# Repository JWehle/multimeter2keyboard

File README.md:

# multimeter2keyboard
A board that reads 38XR-A multimeter infrared port outputs and converts them to PC keyboard inputs.

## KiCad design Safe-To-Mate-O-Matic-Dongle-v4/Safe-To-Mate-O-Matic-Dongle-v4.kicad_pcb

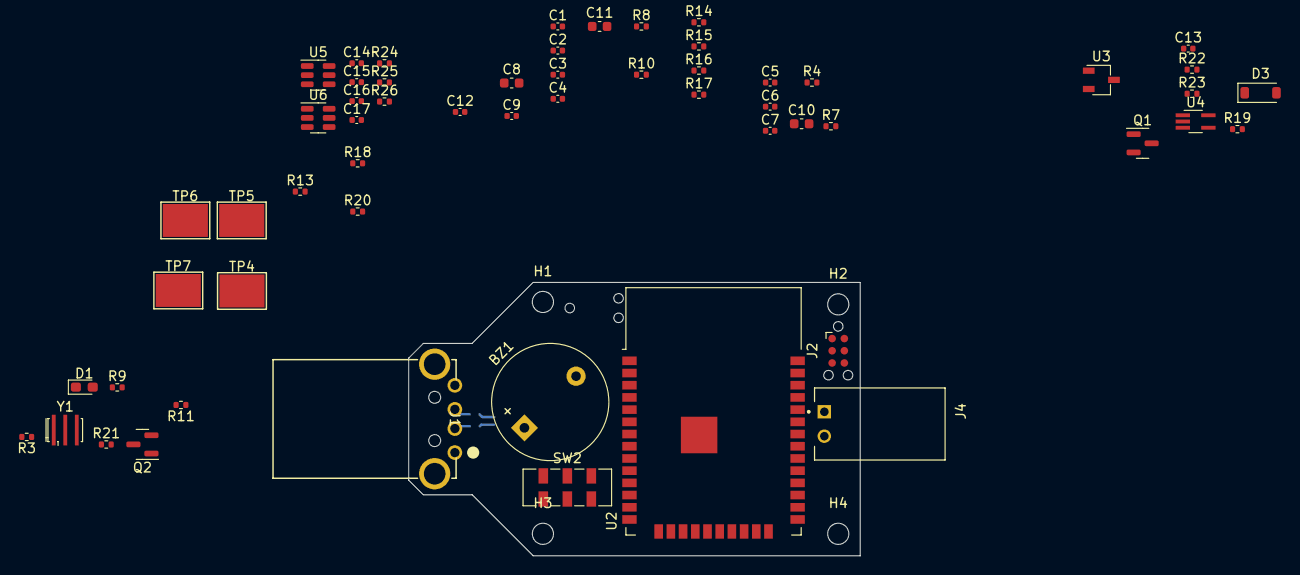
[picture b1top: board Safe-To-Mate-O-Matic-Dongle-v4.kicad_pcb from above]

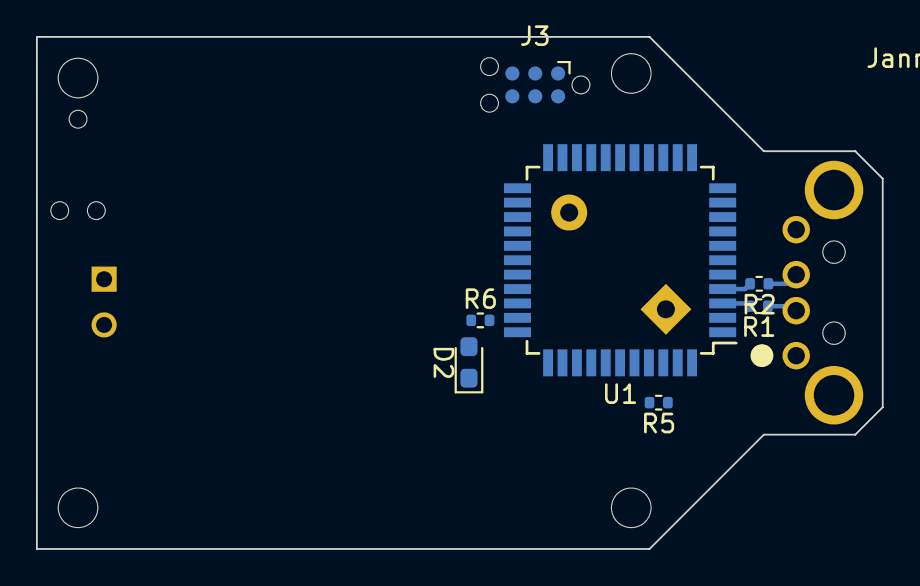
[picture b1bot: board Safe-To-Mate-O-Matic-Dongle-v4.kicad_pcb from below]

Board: 4 copper layers, 47.0 x 28.4 mm, 68 parts (7 on the bottom side), 46 nets.

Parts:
BZ1: WST-1210T; Buzzer_12x9.5RM7.6
C1, C2, C3, C4: 1uF; C_0402_1005Metric
C5, C6, C7, C9, C12, C13, C14, C15, C16, C17: 0.1uF; C_0402_1005Metric
C8, C10, C11: 10uF; C_0603_1608Metric
D1, D2: GREEN LED; LED_0603_1608Metric_Pad1.05x0.95mm_HandSolder
D3: 1N4148W; D_SOD-123
H1, H2, H3, H4: M2; MountingHole_2.2mm_M2
J1: USB_A; USB_MALE_A_480370001
J2, J3: TC2030-IDC-NL; Tag-Connect_TC2030-IDC-NL_2x03_P1.27mm_Vertical
J4: 103906-1; TE_103906-1
Q1, Q2: MMBT3904; SOT-23
R1, R2, R5: 22; R_0402_1005Metric
R3, R4, R7, R8, R14, R15, R16, R17, R18, R19, R20, R21, R22, R23, R24, R26: 10K; R_0402_1005Metric
R6, R9: 1K; R_0402_1005Metric
R10, R11, R25: 0; R_0402_1005Metric
R13: 1Meg; R_0402_1005Metric
SW2: JS202011JCQN; SW_DPDT_CK_JS202011JCQN
TP4, TP5, TP6, TP7: 5016; TestPoint_Keystone_5016_Compact
U1: ATmega32U4-A; TQFP-44_10x10mm_P0.8mm
U2: ESP32-WROOM-32D; ESP32-WROOM-32D_no_vias
U3: AP2138N-3.3TRG1; TSOT-23
U4: 74AHC1G14SE-7; SOT-353_SC-70-5_Handsoldering
U5, U6: SN74LVC1T45DBV; SOT-23-6
Y1: CSTNE16M0V530000R0; Resonator_SMD_Murata_CSTxExxV-3Pin_3.0x1.1mm_HandSoldering

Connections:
+3.3V: C8.1, C9.1, C12.1, C15.1, C17.1, J2.2, R7.1, R8.1, R10.1, R15.1, R20.1, R23.1, TP7.1, U2.2 (VDD), U4.5 (VCC), U5.6 (VCCB), U6.6 (VCCB)
+5V: C2.1, C4.1, C5.1, C6.1, C7.1, C10.1, C14.1, C16.1, J1.1 (VBUS), J3.2, R3.1, R4.1, R14.1, R21.1, R25.2, TP6.1, U1.2 (UVCC), U1.7 (VBUS), U1.14 (VCC), U1.24 (AVCC), U1.34 (VCC), U1.44 (AVCC), U3.3 (VI), U5.1 (VCCA), U6.1 (VCCA)
/+3.3V_PRE: C11.1, R10.2, U3.2 (VO)
/ATMEGA_LED: R6.2, U1.32 (PC7)
/ESP32_LED: R9.2, U2.24 (IO2)
ATMEGA_BUTTON: Q2.3 (C), R21.2, U1.18 (PD0)
ATMEGA_LN: SW2.2 (B), U1.19 (PD1)
ESP32_BOOT0: J2.5, R8.2, U2.25 (IO0)
ESP32_BUTTON: Q1.3 (C), R20.2, U2.13 (IO14)
ESP32_EN: J2.4, R7.2, U2.3 (EN)
ESP32_LN: SW2.5 (B), U2.16 (IO13)
GND: BZ1.2 (+), C1.2, C2.2, C3.2, C4.2, C5.2, C6.2, C7.2, C8.2, C9.2, C10.2, C11.2, C12.2, C13.2, C14.2, C15.2, C16.2, C17.2, D1.1 (K), D2.1 (K), J1.4 (GND), J2.6, J3.6, J4.2, Q1.2 (E), Q2.2 (E), R11.2, R13.2, R16.2, R17.2, R24.2, R26.2, TP4.1, TP5.1, U1.5 (UGND), U1.15 (GND), U1.23 (GND), U1.35 (GND), U1.43 (GND), U2.1 (GND), U2.15 (GND), U2.38 (GND), U2.39 (GND), U3.1 (GND), U4.3 (GND), U5.2 (GND), U6.2 (GND), Y1.2
MISO: J3.1, U1.11 (PB3)
MOSI: J3.4, U1.10 (PB2)
unnamed: BZ1.1 (-), R5.1
unnamed: D1.2 (A), R9.1
unnamed: D2.2 (A), R6.1
unnamed: D3.2 (A), J4.1, R22.2, R23.2
unnamed: C13.1, D3.1 (K), R22.1, U4.2
unnamed: J1.3 (D+), R2.1
unnamed: J1.2 (D-), R1.1
unnamed: Q1.1 (B), R19.1
unnamed: Q2.1 (B), R18.1
unnamed: R18.2, R19.2, U4.4
unnamed: R14.2, SW2.1 (A)
unnamed: R16.1, SW2.3 (C)
unnamed: R15.2, SW2.4 (A)
unnamed: R17.1, SW2.6 (C)
unnamed: C1.1, U1.42 (AREF)
unnamed: R2.2, U1.4 (D+)
unnamed: R1.2, U1.3 (D-)
unnamed: R5.2, U1.29 (PB5)
unnamed: C3.1, U1.6 (UCAP)
unnamed: U1.17 (XTAL1), Y1.3
unnamed: U1.16 (XTAL2), Y1.1
unnamed: R4.2, U1.33 (~HWB/PE2)
unnamed: R25.1, U5.5 (DIR)
unnamed: R11.1, U6.5 (DIR)
RESET: J3.5, R3.2, U1.13 (~RESET)
RX: U1.20 (PD2), U6.3 (A)
RXD0: J2.3, U2.34 (RXD0/IO3)
RXD2: U2.27 (IO16), U5.4 (B)
SCK: J3.3, U1.9 (PB1)
TX: R24.1, U1.21 (PD3), U5.3 (A)
TXD0: J2.1, U2.35 (TXD0/IO1)
TXD2: R26.1, U2.28 (IO17), U6.4 (B)

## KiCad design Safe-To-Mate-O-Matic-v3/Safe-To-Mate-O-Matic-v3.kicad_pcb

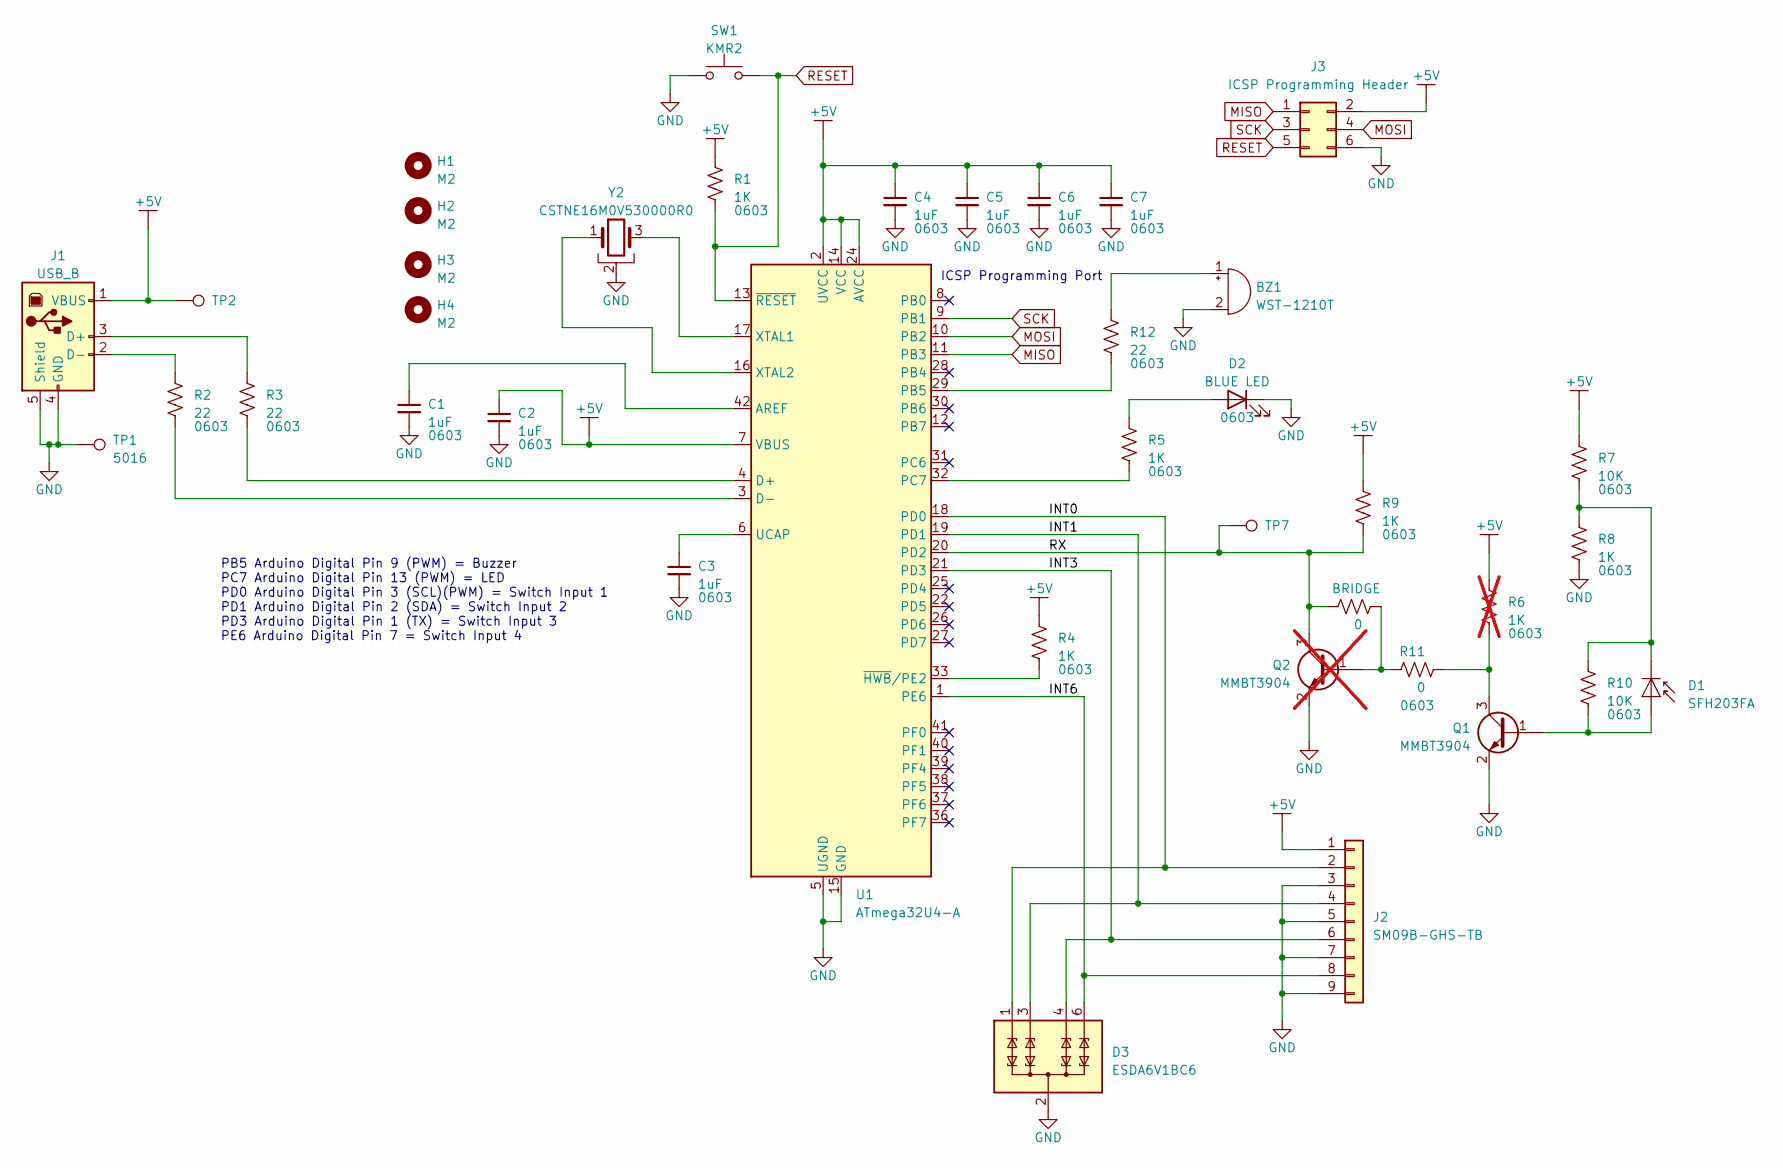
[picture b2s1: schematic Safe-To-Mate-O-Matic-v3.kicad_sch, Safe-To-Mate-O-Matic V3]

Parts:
BRIDGE: 0; R_0603_1608Metric_Pad0.98x0.95mm_HandSolder
BZ1: WST-1210T; Buzzer_12x9.5RM7.6
C1, C2, C3, C4, C5, C6, C7: 1uF; C_0603_1608Metric_Pad1.08x0.95mm_HandSolder
D1: SFH203FA; LED_D5.0mm_IRGrey
D2: BLUE LED; LED_0603_1608Metric_Pad1.05x0.95mm_HandSolder
D3: ESDA6V1BC6; SOT-23-6
H1, H2, H3, H4: M2; MountingHole_2.2mm_M2
J1: USB_B; USB_B_OST_USB-B1HSxx_Horizontal
J2: SM09B-GHS-TB; JST_GH_SM09B-GHS-TB_1x09-1MP_P1.25mm_Horizontal
J3: ICSP Programming Header; PinHeader_2x03_P2.54mm_Vertical_SMD
Q1: MMBT3904; SOT-23
Q2: MMBT3904; SOT-23; not fitted
R1, R4, R5, R8, R9: 1K; R_0603_1608Metric_Pad0.98x0.95mm_HandSolder
R2, R3, R12: 22; R_0603_1608Metric_Pad0.98x0.95mm_HandSolder
R6: 1K; R_0603_1608Metric_Pad0.98x0.95mm_HandSolder; not fitted
R7, R10: 10K; R_0603_1608Metric_Pad0.98x0.95mm_HandSolder
R11: 0; R_0603_1608Metric_Pad0.98x0.95mm_HandSolder
SW1: KMR2; SW_Push_1P1T_NO_CK_KMR2
TP1: 5016; TestPoint_Keystone_5016_Compact
TP2, TP7: D1.5mm; TestPoint_Pad_D1.5mm
U1: ATmega32U4-A; TQFP-44_10x10mm_P0.8mm
Y2: CSTNE16M0V530000R0; Resonator_SMD_Murata_CSTxExxV-3Pin_3.0x1.1mm_HandSoldering

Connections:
+5V: C2.1, C4.1, C5.1, C6.1, C7.1, J1.1 (VBUS), J2.1, J3.2, R1.1, R4.1, R6.1, R7.1, R9.1, TP2.1, U1.2 (UVCC), U1.7 (VBUS), U1.14 (VCC), U1.24 (AVCC), U1.34 (VCC), U1.44 (AVCC)
/INT0: D3.1 (TVS1), J2.2, U1.18 (PD0)
/INT1: D3.3 (TVS2), J2.4, U1.19 (PD1)
/INT3: D3.4 (TVS3), J2.6, U1.21 (PD3)
/INT6: D3.6 (TVS4), J2.8, U1.1 (PE6)
/RX: BRIDGE.1, Q2.3 (C), R9.2, TP7.1, U1.20 (PD2)
GND: BZ1.2 (+), C1.2, C2.2, C3.2, C4.2, C5.2, C6.2, C7.2, D2.1 (K), D3.2 (COM), D3.5 (COM), J1.4 (GND), J1.5 (Shield), J2.3, J2.5, J2.7, J2.9, J3.6, Q1.2 (E), Q2.2 (E), R8.2, SW1.1, TP1.1, U1.5 (UGND), U1.15 (GND), U1.23 (GND), U1.35 (GND), U1.43 (GND), Y2.2
MISO: J3.1, U1.11 (PB3)
MOSI: J3.4, U1.10 (PB2)
unnamed: BZ1.1 (-), R12.1
unnamed: D1.2 (A), Q1.1 (B), R10.2
unnamed: D1.1 (K), R7.2, R8.1, R10.1
unnamed: D2.2 (A), R5.1
unnamed: J1.3 (D+), R3.1
unnamed: J1.2 (D-), R2.1
unnamed: Q1.3 (C), R6.2, R11.2
unnamed: BRIDGE.2, Q2.1 (B), R11.1
unnamed: C1.1, U1.42 (AREF)
unnamed: R3.2, U1.4 (D+)
unnamed: R2.2, U1.3 (D-)
unnamed: R12.2, U1.29 (PB5)
unnamed: R5.2, U1.32 (PC7)
unnamed: C3.1, U1.6 (UCAP)
unnamed: U1.17 (XTAL1), Y2.3
unnamed: U1.16 (XTAL2), Y2.1
unnamed: R4.2, U1.33 (~HWB/PE2)
RESET: J3.5, R1.2, SW1.2, U1.13 (~RESET)
SCK: J3.3, U1.9 (PB1)

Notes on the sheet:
ICSP Programming Port
PB5 Arduino Digital Pin 9 (PWM) = Buzzer PC7 Arduino Digital Pin 13 (PWM) = LED PD0 Arduino Digital Pin 3 (SCL)(PWM) = Switch Input 1 PD1 Arduino Digital Pin 2 (SDA) = Switch Input 2 PD3 Arduino Digital Pin 1 (TX) = Switch Input 3 PE6 Arduino Digital Pin 7 = Switch Input 4

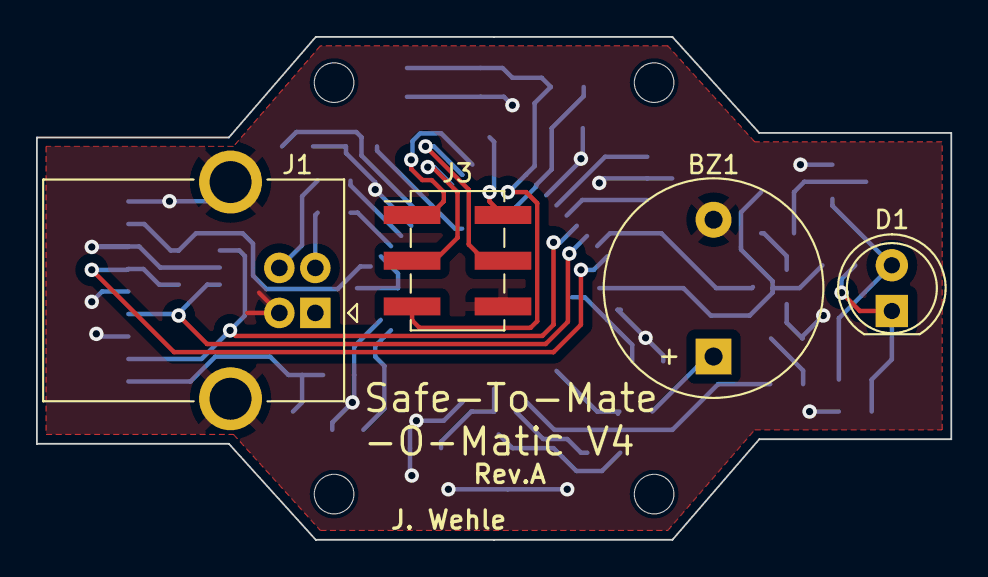
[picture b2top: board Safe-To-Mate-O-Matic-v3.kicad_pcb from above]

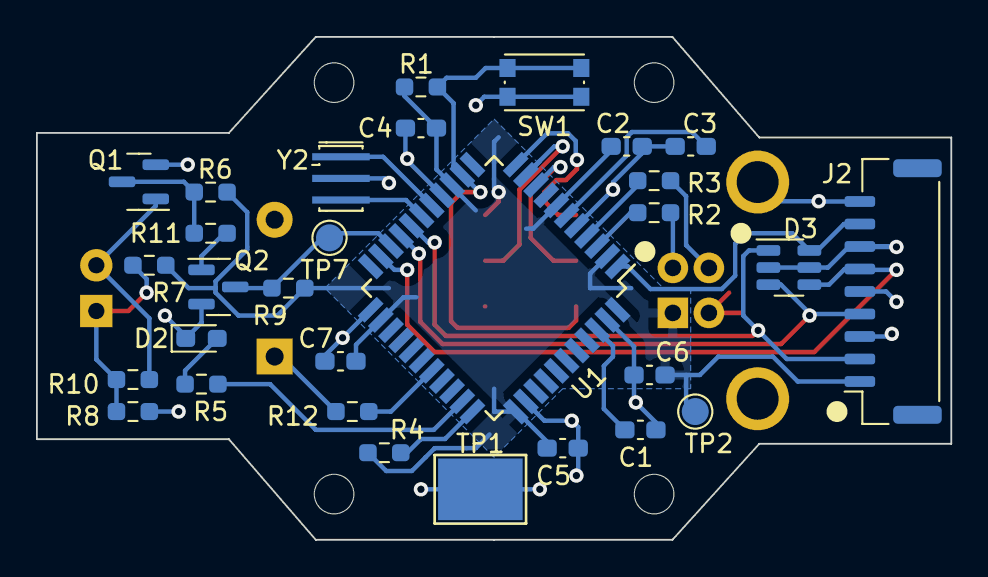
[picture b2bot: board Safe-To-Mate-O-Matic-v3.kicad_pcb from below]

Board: 2 copper layers, 50.8 x 27.9 mm, 38 parts (30 on the bottom side), 28 nets.

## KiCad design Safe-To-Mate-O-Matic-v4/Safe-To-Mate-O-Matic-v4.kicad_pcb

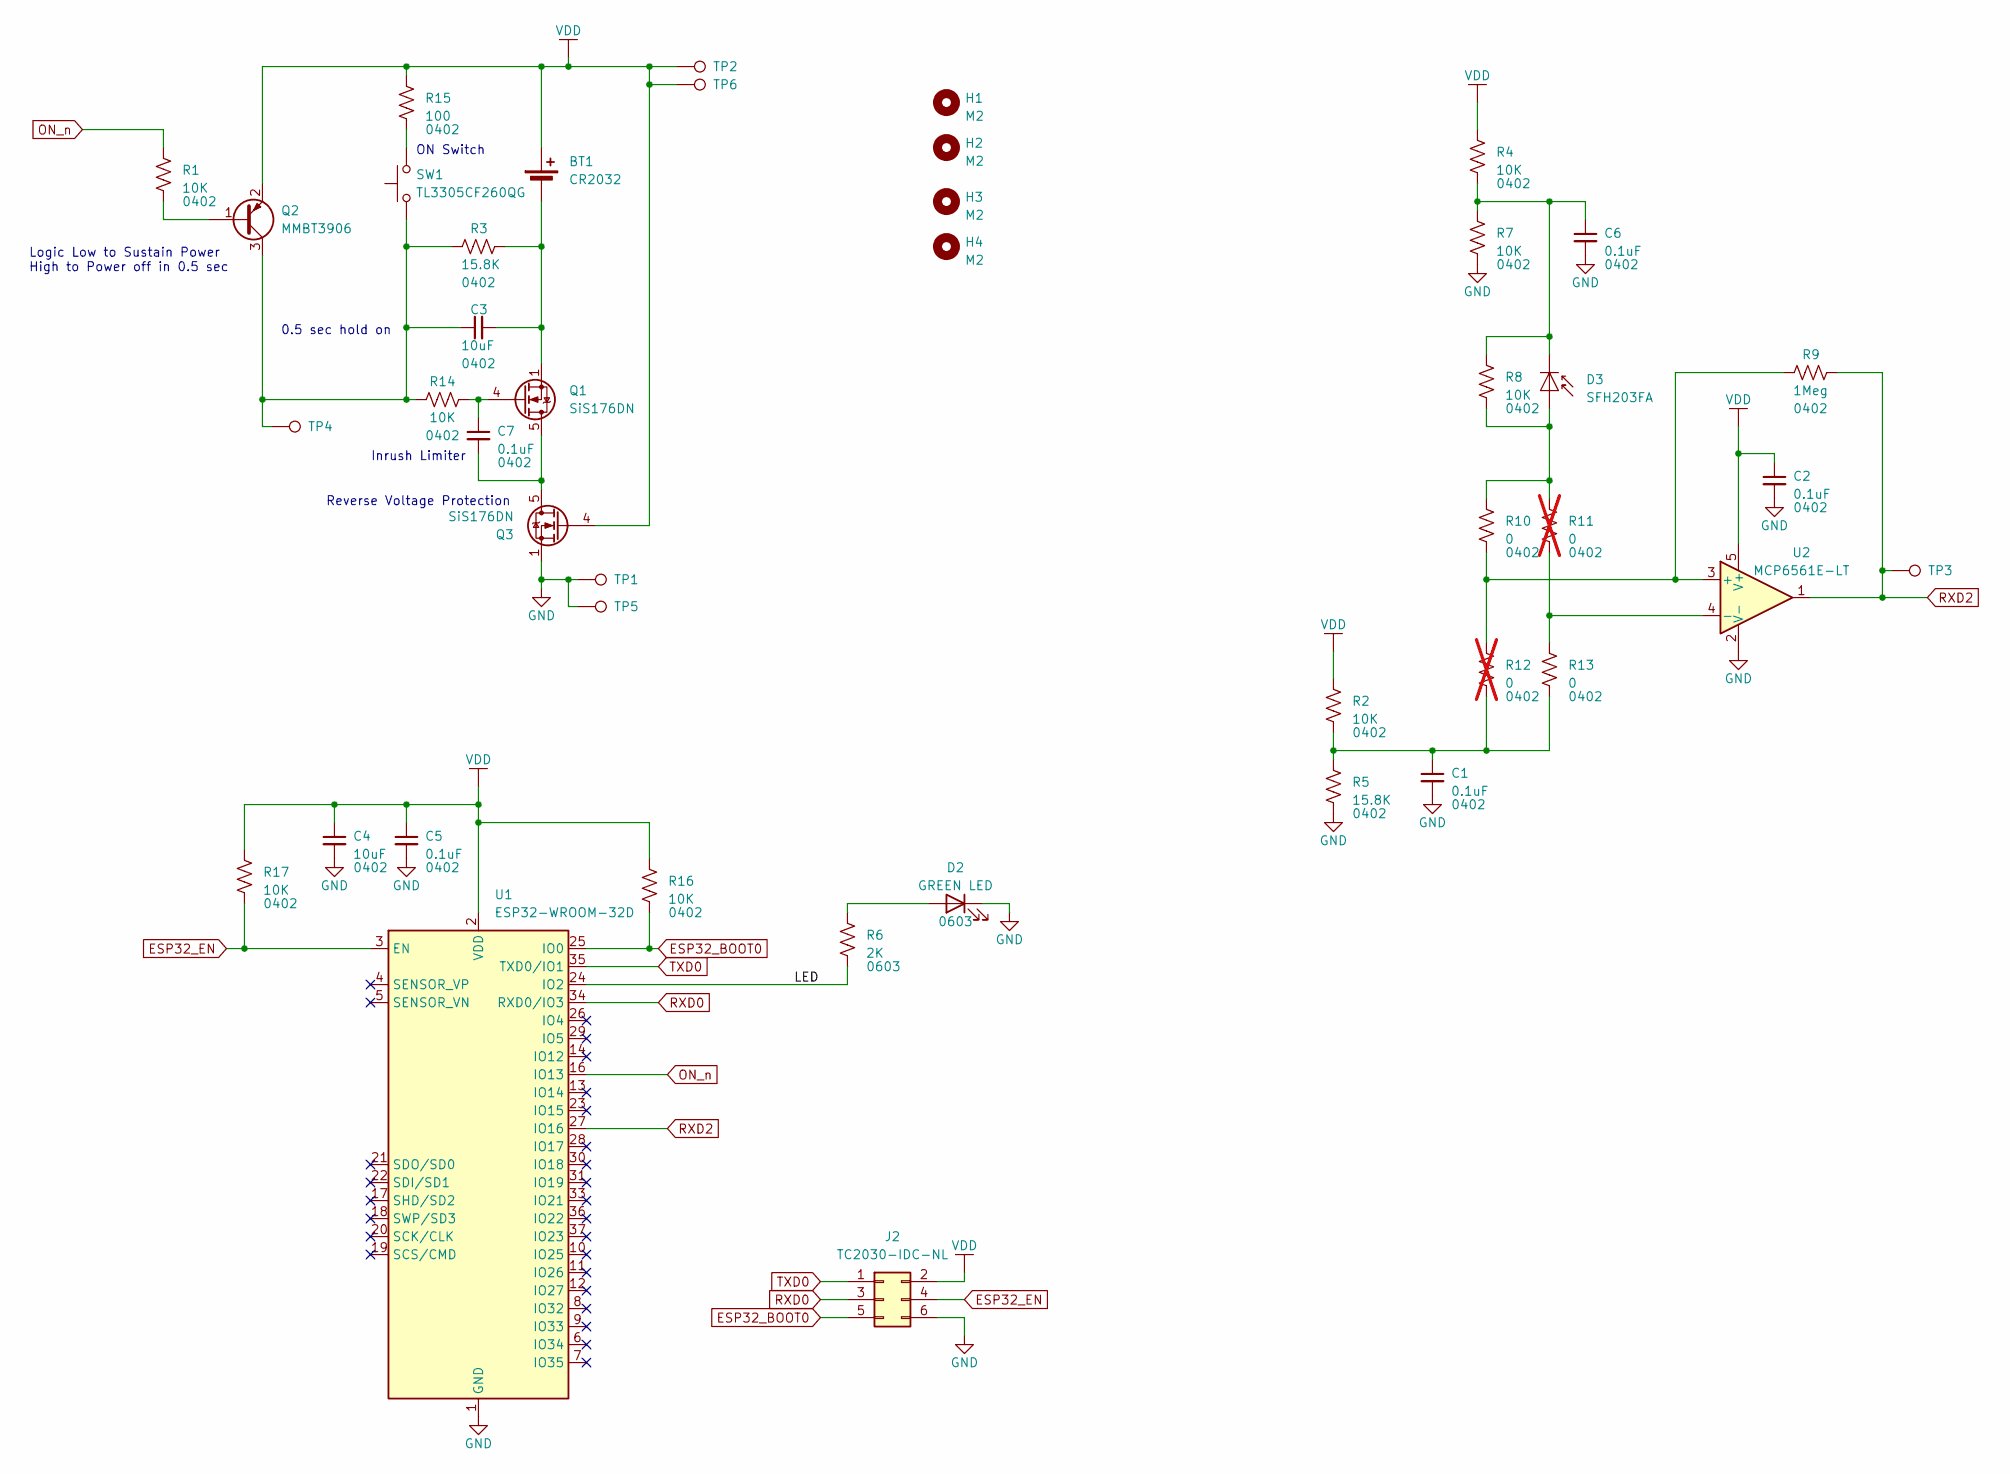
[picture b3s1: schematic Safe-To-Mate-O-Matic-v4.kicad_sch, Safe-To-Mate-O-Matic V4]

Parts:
BT1: CR2032; BatteryHolder_Keystone_3034_1x20mm; Part Number 3034
C1, C2, C5, C6, C7: 0.1uF; C_0402_1005Metric
C3, C4: 10uF; C_0402_1005Metric; Part Number GRM155R60J106ME05D
D2: GREEN LED; LED_0603_1608Metric_Pad1.05x0.95mm_HandSolder
D3: SFH203FA; LED_D5.0mm_IRGrey; Part Number SFH203FA
H1, H2, H3, H4: M2; MountingHole_2.2mm_M2
J2: TC2030-IDC-NL; Tag-Connect_TC2030-IDC-NL_2x03_P1.27mm_Vertical; Part Number TC2030-IDC-NL
Q1, Q3: SiS176DN; Vishay_PowerPAK_1212-8_Single; Part Number SiS176DN
Q2: MMBT3906; SOT-23; Part Number MMBT3906
R1, R2, R4, R7, R8, R14, R16, R17: 10K; R_0402_1005Metric
R3, R5: 15.8K; R_0402_1005Metric
R6: 2K; R_0603_1608Metric_Pad0.98x0.95mm_HandSolder
R9: 1Meg; R_0402_1005Metric
R10, R13: 0; R_0402_1005Metric
R11, R12: 0; R_0402_1005Metric; not fitted
R15: 100; R_0402_1005Metric
SW1: TL3305CF260QG; SW_SPST_TL3305C; Part Number TL3305CF260QG
TP1, TP2, TP3, TP4, TP5, TP6: D1.5mm; TestPoint_Pad_D1.5mm
U1: ESP32-WROOM-32D; ESP32-WROOM-32D_no_vias; Part Number ESP32-WROOM-32D
U2: MCP6561E-LT; SOT-353_SC-70-5; Part Number MCP6561E-LT

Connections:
/LED: R6.2, U1.24 (IO2)
ESP32_BOOT0: J2.5, R16.2, U1.25 (IO0)
ESP32_EN: J2.4, R17.2, U1.3 (EN)
GND: C1.2, C2.2, C4.2, C5.2, C6.2, D2.1 (K), J2.6, Q3.1 (S), Q3.2 (S), Q3.3 (S), R5.2, R7.2, TP1.1, TP5.1, U1.1 (GND), U1.15 (GND), U1.38 (GND), U1.39 (GND), U2.2 (V-)
unnamed: BT1.2 (-), C3.2, Q1.1 (S), Q1.2 (S), Q1.3 (S), R3.2
unnamed: C1.1, R2.2, R5.1, R12.2, R13.2
unnamed: D2.2 (A), R6.1
unnamed: D3.2 (A), R8.2, R10.1, R11.1
unnamed: C6.1, D3.1 (K), R4.2, R7.1, R8.1
unnamed: C7.2, Q1.5 (D), Q3.5 (D)
unnamed: C7.1, Q1.4 (G), R14.2
unnamed: Q2.1 (B), R1.2
unnamed: C3.1, Q2.3 (C), R3.1, R14.1, SW1.1, TP4.1
unnamed: R15.2, SW1.2
unnamed: R9.1, R10.2, R12.1, U2.3 (+)
unnamed: R11.2, R13.1, U2.4 (-)
ON_n: R1.1, U1.16 (IO13)
RXD0: J2.3, U1.34 (RXD0/IO3)
RXD2: R9.2, TP3.1, U1.27 (IO16), U2.1
TXD0: J2.1, U1.35 (TXD0/IO1)
VDD: BT1.1 (+), C2.1, C4.1, C5.1, J2.2, Q2.2 (E), Q3.4 (G), R2.1, R4.1, R15.1, R16.1, R17.1, TP2.1, TP6.1, U1.2 (VDD), U2.5 (V+)

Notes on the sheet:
Inrush Limiter
Logic Low to Sustain Power High to Power off in 0.5 sec
ON Switch
Reverse Voltage Protection
0.5 sec hold on

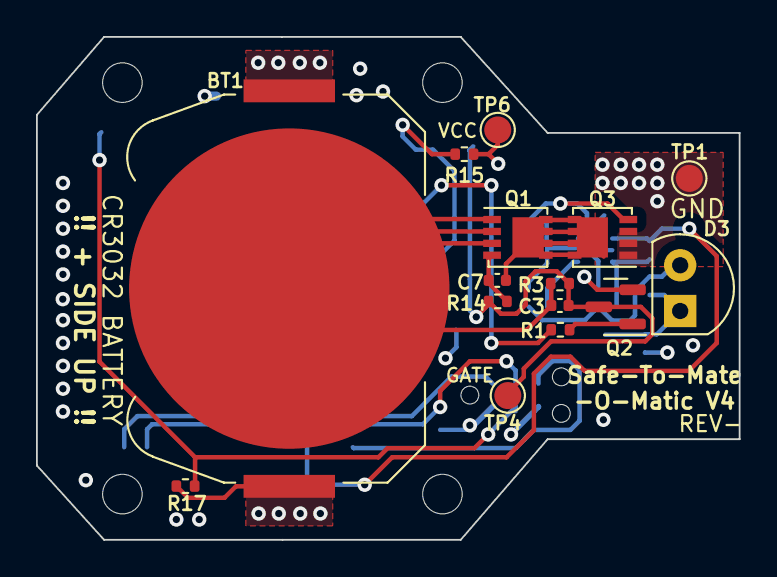
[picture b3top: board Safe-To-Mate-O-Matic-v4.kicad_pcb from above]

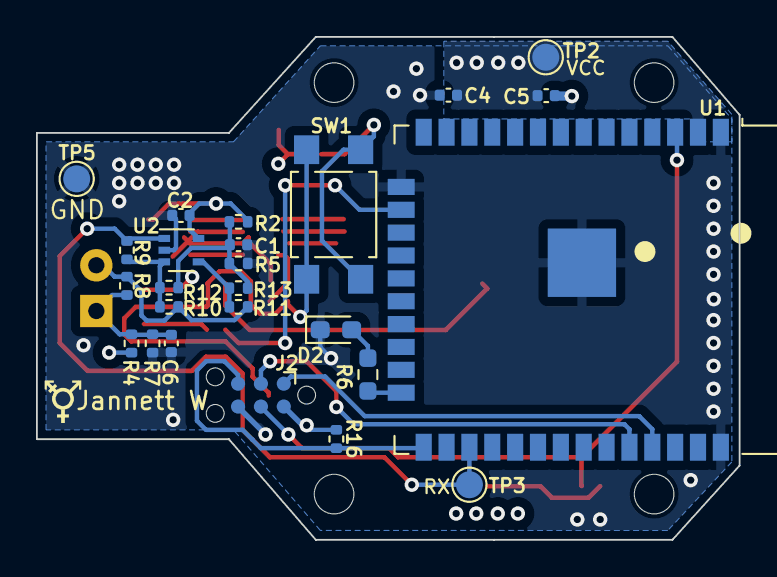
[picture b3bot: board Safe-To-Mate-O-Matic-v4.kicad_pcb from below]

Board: 4 copper layers, 39.0 x 27.9 mm, 44 parts (25 on the bottom side), 21 nets.

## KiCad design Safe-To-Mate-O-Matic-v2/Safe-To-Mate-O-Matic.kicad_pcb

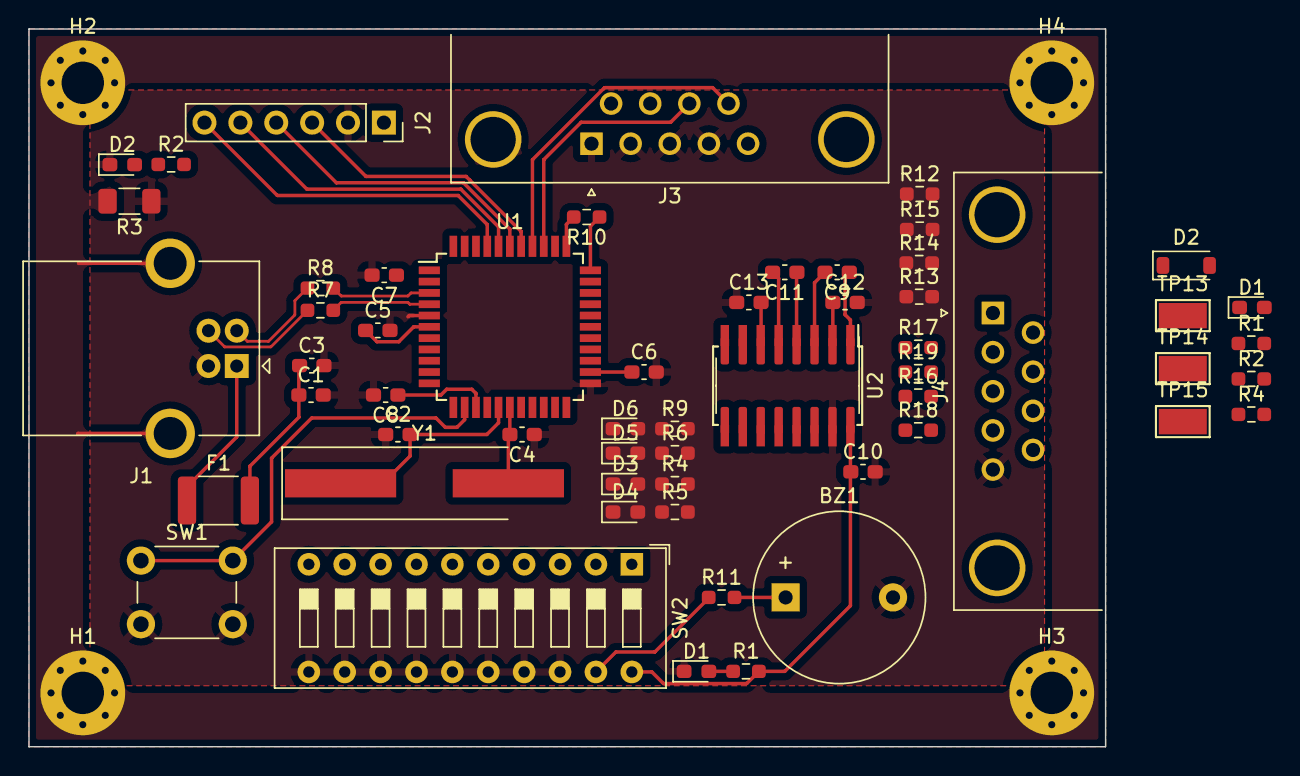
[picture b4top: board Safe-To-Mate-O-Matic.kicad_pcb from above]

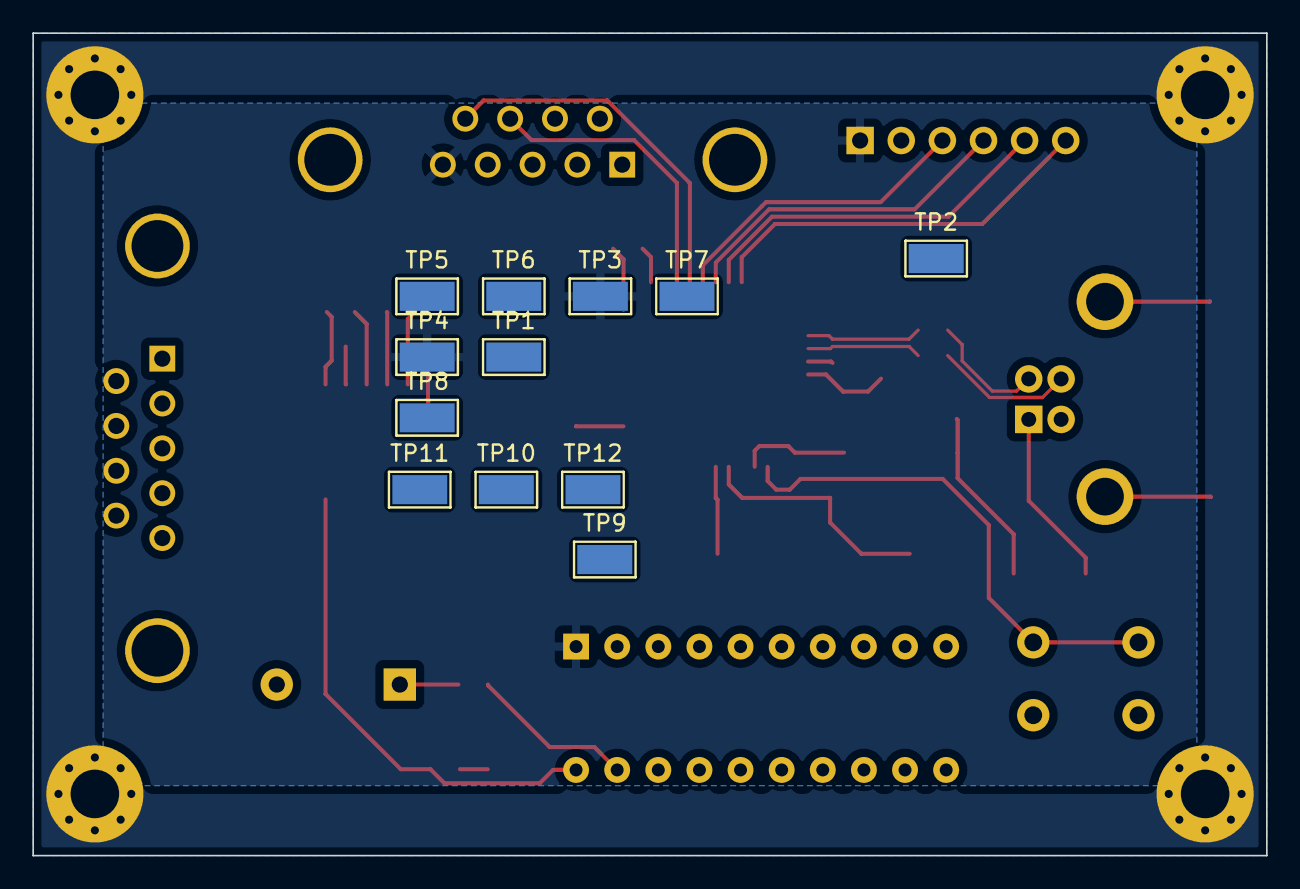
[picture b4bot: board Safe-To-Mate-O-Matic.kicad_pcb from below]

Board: 2 copper layers, 76.2 x 50.8 mm, 74 parts (12 on the bottom side), 71 nets.

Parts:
BZ1: WST-1210T; Buzzer_12x9.5RM7.6
C1, C8: 10uF; C_0603_1608Metric_Pad1.08x0.95mm_HandSolder
C2, C4: 18pF; C_0603_1608Metric_Pad1.08x0.95mm_HandSolder
C3, C5: 1uF; C_0603_1608Metric_Pad1.08x0.95mm_HandSolder
C6, C7, C9, C10, C11, C12, C13: 0.1uF; C_0603_1608Metric_Pad1.08x0.95mm_HandSolder
D1, D2#2, D3, D4, D5: BLUE; LED_0603_1608Metric_Pad1.05x0.95mm_HandSolder
D1#2, D6: RED; LED_0603_1608Metric_Pad1.05x0.95mm_HandSolder
D2: 1N4148W; D_SOD-123
F1: 500mA; R_1812_4532Metric_Pad1.30x3.40mm_HandSolder
H1, H2, H3, H4: M3; MountingHole_3mm_Pad_Via
J1: USB_B; USB_B_OST_USB-B1HSxx_Horizontal
J2: Conn_01x06_2.54mm; PinSocket_1x06_P2.54mm_Vertical
J3, J4: DB9_Male_MountingHoles; DSUB-9_Female_Horizontal_P2.77x2.84mm_EdgePinOffset4.94mm_H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
R1, R2, R2#2, R4, R5, R6, R9, R10, R11: 1k; R_0603_1608Metric_Pad0.98x0.95mm_HandSolder
R1#2, R12, R13, R14, R15, R16, R17, R18, R19: 0; R_0603_1608Metric_Pad0.98x0.95mm_HandSolder
R3: 1Meg; R_1206_3216Metric_Pad1.30x1.75mm_HandSolder
R4#2: 10k; R_0603_1608Metric_Pad0.98x0.95mm_HandSolder
R7, R8: 22; R_0603_1608Metric_Pad0.98x0.95mm_HandSolder
SW1: SW_Push; SW_PUSH_6mm
SW2: SW_DIP_x10; SW_DIP_SPSTx10_Slide_9.78x27.58mm_W7.62mm_P2.54mm
TP1, TP2, TP3, TP4, TP5, TP6, TP7, TP8, TP9, TP10, TP11, TP12, TP13, TP14, TP15: TestPoint; TestPoint_Keystone_5015_Micro-Minature
U1: ATmega32U4-A; TQFP-44_10x10mm_P0.8mm
U2: MAX3232; SOIC-16W_5.3x10.2mm_P1.27mm
U3: MAX3232; SOIC-16_3.9x9.9mm_P1.27mm
Y1: 16MHz; Crystal_SMD_HC49-SD_HandSoldering

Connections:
+3.3V: C5.1, U1.6 (UCAP)
+5V: C1.1, C3.1, C6.1, C7.1, C8.1, D2.1 (K), F1.2, J2.1, R2.2, R2#2.2, R4.2, R4#2.2, R5.2, R6.2, R10.2, SW2.1, TP3.1, TP4.1, U1.2 (UVCC), U1.7 (VBUS), U1.14 (VCC), U1.24 (AVCC), U1.34 (VCC), U1.42 (AREF), U1.44 (AVCC)
/5V_RS232: C10.1, R1.2, SW2.20, U2.16 (VCC), U3.16 (VCC)
/A0: J3.3, U1.36 (PF7)
/A1: J3.7, U1.37 (PF6)
/A2: J2.3, J3.2, U1.38 (PF5)
/A3: J2.4, TP13.1, U1.39 (PF4)
/A4: J2.5, TP14.1, U1.40 (PF1)
/A5: J2.6, TP15.1, U1.41 (PF0)
/BUZZER: R11.1, SW2.19
/BUZZER_OUT: BZ1.1 (-), R11.2
/D+: R7.2, U1.4 (D+)
/D-: R8.2, U1.3 (D-)
/DIN+: J1.3 (D+), R7.1
/DIN-: J1.2 (D-), R8.1
/HWB: R10.1, U1.33 (~HWB/PE2)
/IO0_RX: R14.1, TP7.1, U1.20 (PD2)
/IO1_TX: R12.1, TP5.1, U1.21 (PD3)
/IO2: J3.9, U1.19 (PD1)
/IO3: J3.4, U1.18 (PD0)
/IO4: SW2.3, U1.25 (PD4)
/IO5: R15.1, TP8.1, U1.31 (PC6)
/IO6: SW2.4, U1.27 (PD7)
/IO7: J3.8, U1.1 (PE6)
/IO8: SW2.8, U1.28 (PB4)
/IO9: SW2.2, U1.29 (PB5)
/IO10: SW2.9, U1.30 (PB6)
/IO11: R13.1, TP6.1, U1.12 (PB7)
/IO12: D3.1 (K), U1.26 (PD6)
/IO13: R9.2, U1.32 (PC7)
/IO14: SW2.7, U1.11 (PB3)
/IO15: SW2.5, U1.9 (PB1)
/IO16: SW2.6, U1.10 (PB2)
/RST: D2.2 (A), R4#2.1, SW1.1, U1.13 (~RESET)
/RXLED: D5.1 (K), U1.8 (PB0)
/TXLED: D4.1 (K), U1.22 (PD5)
/VBUS: F1.1, J1.1 (VBUS)
/XTAL1: C4.2, U1.17 (XTAL1), Y1.2
/XTAL2: C2.2, U1.16 (XTAL2), Y1.1
CGND: H1.1, H2.1, H3.1, H4.1, J1.5 (Shield), J3.0 (PAD), J4.0 (PAD), R3.2
GND: BZ1.2 (+), C1.2, C2.1, C3.2, C4.1, C5.2, C6.2, C7.2, C8.2, C10.2, C12.2, C13.1, D1.1 (K), D1#2.1 (K), D2#2.1 (K), D6.1 (K), J1.4 (GND), J2.2, J3.5, R1#2.1, R3.1, SW1.2, SW2.11, SW2.12, SW2.13, SW2.14, SW2.15, SW2.16, SW2.17, SW2.18, TP1.1, TP2.1, U1.5 (UGND), U1.15 (GND), U1.23 (GND), U1.35 (GND), U1.43 (GND), U2.15 (GND), U3.15 (GND)
unnamed: D1#2.2 (A), R2#2.1
unnamed: D1.2 (A), R1.1
unnamed: D2#2.2 (A), R2.1
unnamed: D3.2 (A), R4.1
unnamed: D4.2 (A), R5.1
unnamed: D5.2 (A), R6.1
unnamed: D6.2 (A), R9.1
unnamed: J4.1, TP12.1
unnamed: J4.2, R17.2
unnamed: J4.3, R16.2
unnamed: J4.4, R18.2
unnamed: J4.5, R1#2.2
unnamed: J4.6, TP11.1
unnamed: J4.7, R19.2
unnamed: J4.8, TP10.1
unnamed: J4.9, TP9.1
unnamed: C9.1, U2.1 (C1+), U3.1 (C1+)
unnamed: C9.2, U2.3 (C1-), U3.3 (C1-)
unnamed: C11.1, U2.4 (C2+), U3.4 (C2+)
unnamed: C11.2, U2.5 (C2-), U3.5 (C2-)
unnamed: R17.1, U2.13 (R1IN), U3.13 (R1IN)
unnamed: R14.2, U2.12 (R1OUT), U3.12 (R1OUT)
unnamed: R19.1, U2.8 (R2IN), U3.8 (R2IN)
unnamed: R15.2, U2.9 (R2OUT), U3.9 (R2OUT)
unnamed: R12.2, U2.11 (T1IN), U3.11 (T1IN)
unnamed: R18.1, U2.14 (T1OUT), U3.14 (T1OUT)
unnamed: R13.2, U2.10 (T2IN), U3.10 (T2IN)
unnamed: R16.1, U2.7 (T2OUT), U3.7 (T2OUT)
unnamed: C12.1, U2.2 (VS+), U3.2 (VS+)
unnamed: C13.2, U2.6 (VS-), U3.6 (VS-)
